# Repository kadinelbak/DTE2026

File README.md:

# DTE 2026

Hardware for the DTE Designathon project.

## EMG + Stretch Sensor Board

KiCad 8 project in [`hardware/emg_board/`](hardware/emg_board/). Open `emg_board.kicad_pro` in KiCad; the symbol and footprint libraries are project-local, so nothing needs to be installed.

```
hardware/emg_board/
├── emg_board.kicad_pro     project
├── emg_board.kicad_sch     schematic
├── emg_board.kicad_pcb     PCB layout
├── EMG_Board.kicad_sym     project symbol library
├── EMG_Board.pretty/       project footprint library (*.kicad_mod)
├── sym-lib-table           points to ${KIPRJMOD}/EMG_Board.kicad_sym
├── fp-lib-table            points to ${KIPRJMOD}/EMG_Board.pretty
└── docs/                   schematic and PCB previews and screenshots
```

The board runs from a 9 V battery through a switch, a reverse-polarity diode and a 7805 regulator into an ESP32 DevKit (38-pin). It carries:

- an EMG front end (instrumentation amp, 8 Hz high-pass, ~800 Hz low-pass, total gain ~1200) on IO34
- a Wheatstone bridge for two stretch sensors on IO35 / IO33
- a potentiometer on IO32
- three indicator LEDs on IO25 / IO26 / IO27

### KiCad screenshots

PCB layout:

Schematic:

## Microcontroller code

Arduino sketches in [`microcontroller_code/`](microcontroller_code/). Each sketch is in a folder with the same name, as the Arduino IDE expects.

- [`WiFi/`](microcontroller_code/WiFi/): ESP32 button that sends a "Danger mode approached, increase stiffness?" alert to the phone and Apple Watch through ntfy.sh. The notification has Increase stiffness and Decrease stiffness buttons that change the stiffness level (0 to 5) on the ESP32, which confirms with a follow-up notification. The LEDs show the stiffness level: green for low (0-1), yellow for medium (2-3) and red for high (4-5). Before building, copy `secrets.example.h` to `secrets.h` and put your WiFi name and password in it. `secrets.h` is git-ignored so the password stays out of the repo.
- [`EMG/`](microcontroller_code/EMG/): samples the EMG signal on A0 at 1200 Hz, cancels 60 Hz mains hum with a one-cycle comb filter, and prints the smoothed muscle-activity envelope over serial at 115200 baud.
- [`RotationalDrive/`](microcontroller_code/RotationalDrive/): reads the outside stretch sensor on A1, zeroes at neutral, and lights a blue warning LED and a blinking red danger LED as the ankle rolls past the limits. Type an angle over serial to calibrate it to degrees (saved to EEPROM), or `z` to re-zero.

## CAD

SolidWorks files for the hydraulic right foot brace are in [`cad/hydraulic_brace/`](cad/hydraulic_brace/): the assembly (`hydraulics brace Assem.SLDASM`), the brace body (`hydraulic right foot brace`), `bottom brace`, `BottomBraceHydraulics`, `InnerBore`, `OuterBore` and `Gasket`. Keep the file names as they are, because the assembly finds its parts by name.

## Images

- [`images/model/`](images/model/): SolidWorks render of the full brace assembly.

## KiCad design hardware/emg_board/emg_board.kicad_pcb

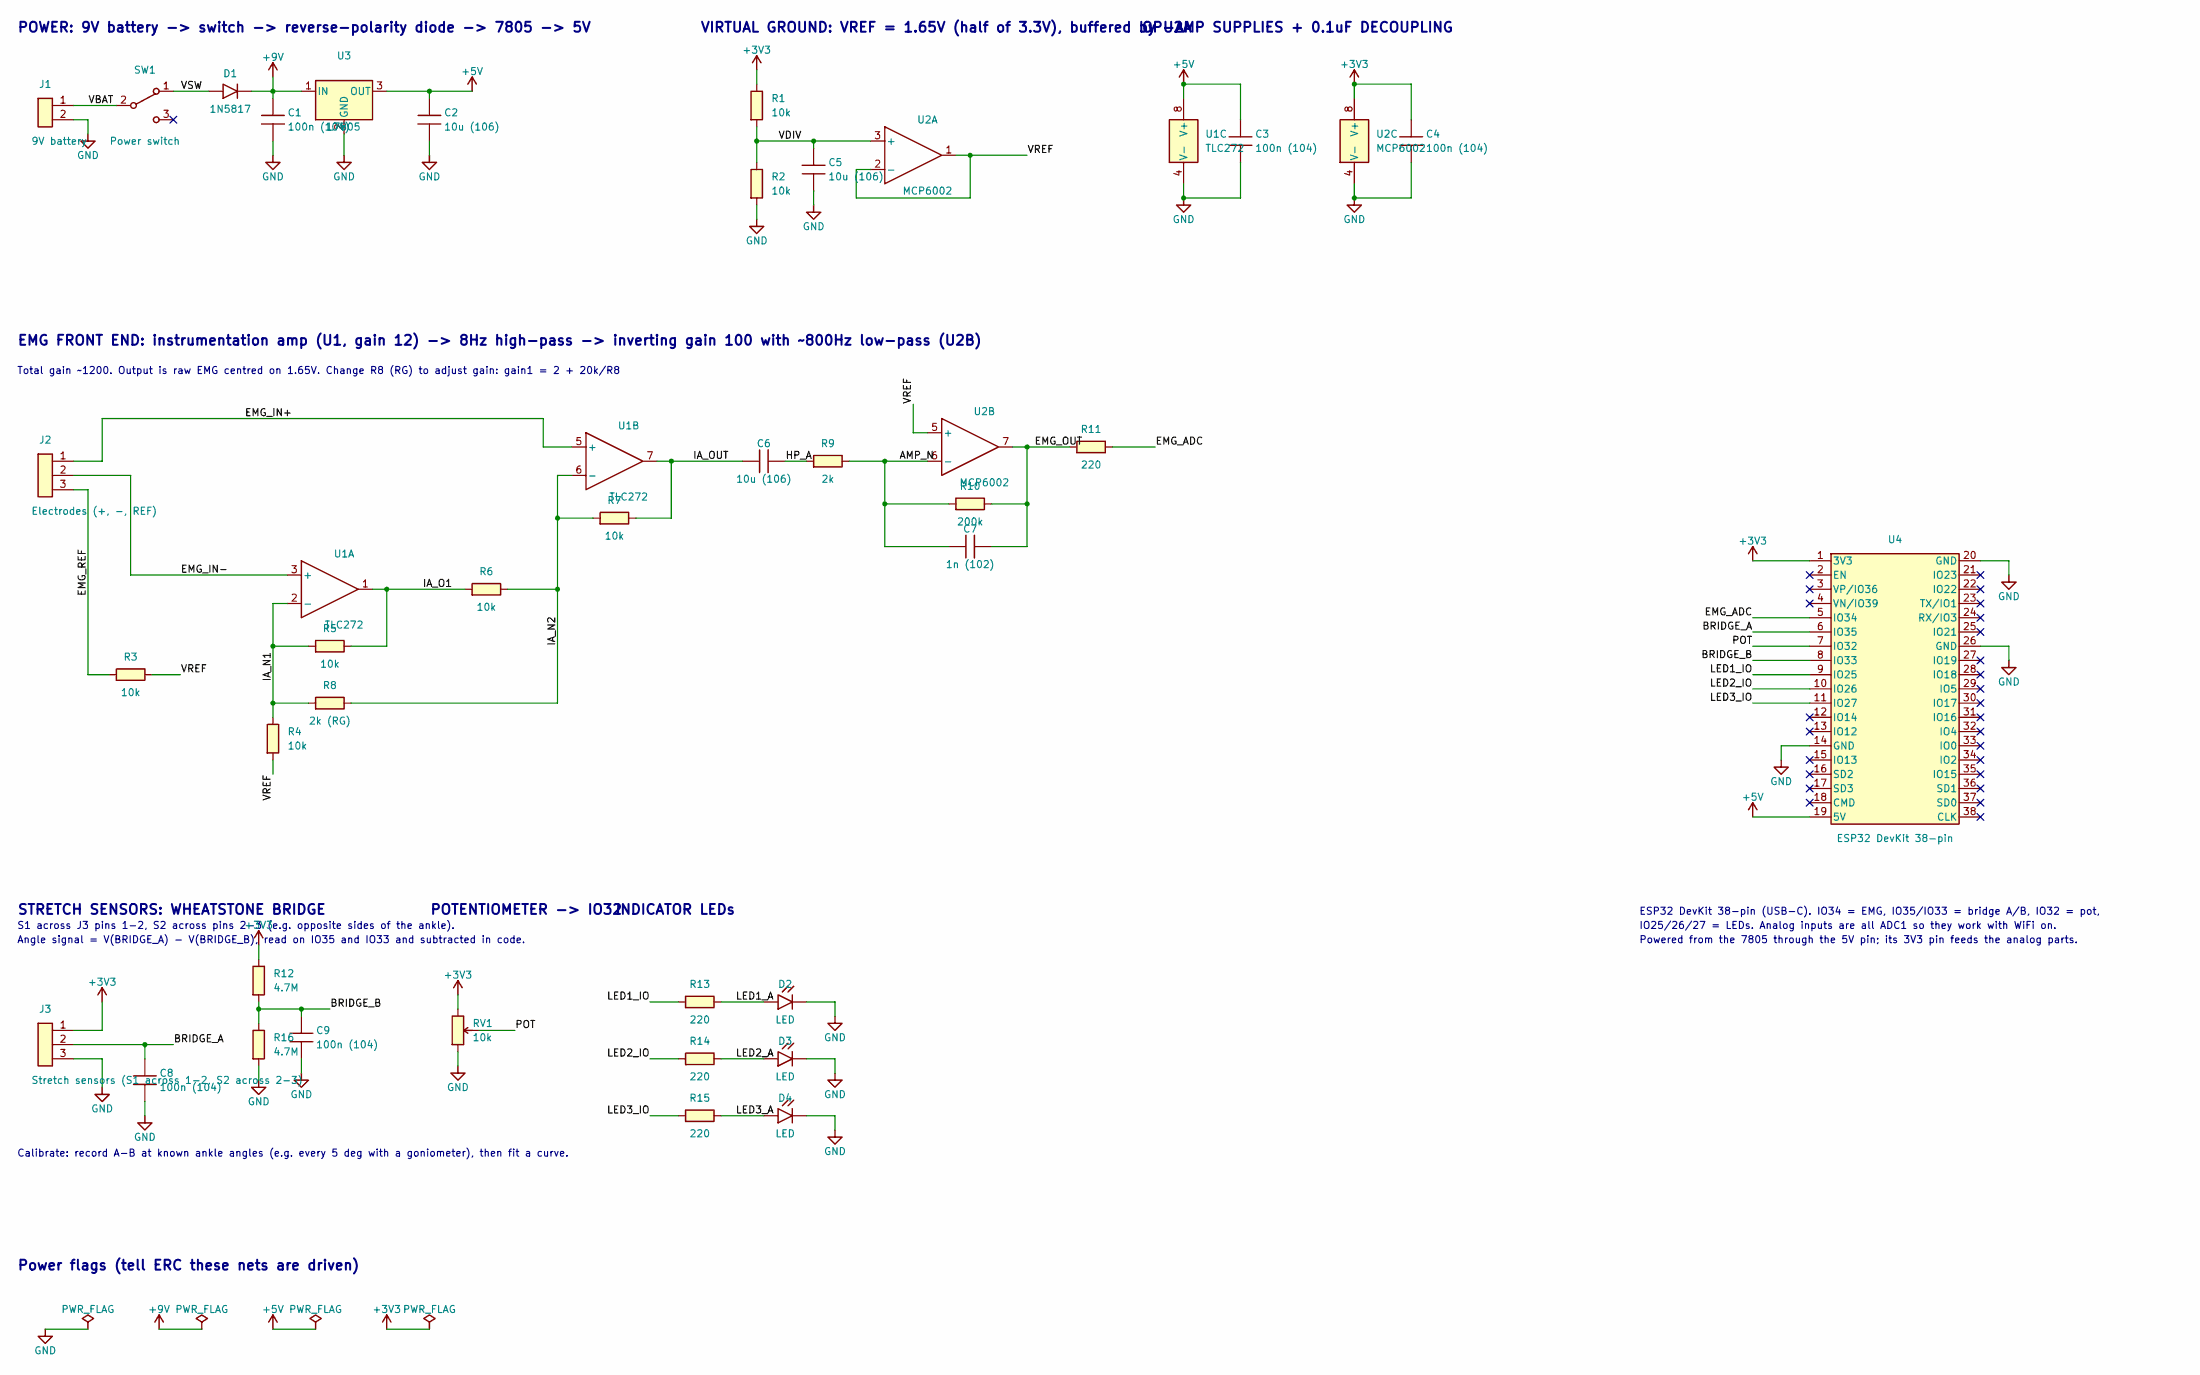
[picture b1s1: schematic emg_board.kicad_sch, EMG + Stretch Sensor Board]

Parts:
C1, C3, C4, C8, C9: 100n (104); C_Disc_P5.08mm
C2, C5, C6: 10u (106); C_Disc_P5.08mm
C7: 1n (102); C_Disc_P5.08mm
D1: 1N5817; D_DO-41_P10.16mm
D2, D3, D4: LED; LED_D5.0mm
J1: 9V battery; TerminalBlock_1x02_P5.08mm
J2: Electrodes (+, -, REF); TerminalBlock_1x03_P5.08mm
J3: Stretch sensors (S1 across 1-2, S2 across 2-3); TerminalBlock_1x03_P5.08mm
R1, R2, R3, R4, R5, R6, R7: 10k; R_Axial_P10.16mm
R8: 2k (RG); R_Axial_P10.16mm
R9: 2k; R_Axial_P10.16mm
R10: 200k; R_Axial_P10.16mm
R11, R13, R14, R15: 220; R_Axial_P10.16mm
R12, R16: 4.7M; R_Axial_P10.16mm
RV1: 10k; Potentiometer_Inline_P2.54mm
SW1: Power switch; SW_Slide_SPDT_P2.54mm
U1: TLC272; DIP-8_W7.62mm
U2: MCP6002; DIP-8_W7.62mm
U3: L7805; TO-220-3_Vertical
U4: ESP32 DevKit 38-pin; ESP32_DevKitC_38pin_W25.4mm

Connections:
+3V3: C4.1, J3.1, R1.1, R12.1, RV1.1, U2.8 (V+), U4.1 (3V3)
+5V: C2.1, C3.1, U1.8 (V+), U3.3 (OUT), U4.19 (5V)
+9V: C1.1, D1.1 (K), U3.1 (IN)
AMP_N: C7.1, R9.2, R10.1, U2.6 (-)
BRIDGE_A: C8.1, J3.2, U4.6 (IO35)
BRIDGE_B: C9.1, R12.2, R16.1, U4.8 (IO33)
EMG_ADC: R11.2, U4.5 (IO34)
EMG_IN+: J2.1, U1.5 (+)
EMG_IN-: J2.2, U1.3 (+)
EMG_OUT: C7.2, R10.2, R11.1, U2.7
EMG_REF: J2.3, R3.1
GND: C1.2, C2.2, C3.2, C4.2, C5.2, C8.2, C9.2, D2.1 (K), D3.1 (K), D4.1 (K), J1.2, J3.3, R2.2, R16.2, RV1.3, U1.4 (V-), U2.4 (V-), U3.2 (GND), U4.14 (GND), U4.20 (GND), U4.26 (GND)
HP_A: C6.2, R9.1
IA_N1: R4.1, R5.1, R8.1, U1.2 (-)
IA_N2: R6.2, R7.1, R8.2, U1.6 (-)
IA_O1: R5.2, R6.1, U1.1
IA_OUT: C6.1, R7.2, U1.7
LED1_A: D2.2 (A), R13.2
LED1_IO: R13.1, U4.9 (IO25)
LED2_A: D3.2 (A), R14.2
LED2_IO: R14.1, U4.10 (IO26)
LED3_A: D4.2 (A), R15.2
LED3_IO: R15.1, U4.11 (IO27)
POT: RV1.2, U4.7 (IO32)
VBAT: J1.1, SW1.2 (B)
VDIV: C5.1, R1.2, R2.1, U2.3 (+)
VREF: R3.2, R4.2, U2.1, U2.2 (-), U2.5 (+)
VSW: D1.2 (A), SW1.1 (A)

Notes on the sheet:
POWER: 9V battery -> switch -> reverse-polarity diode -> 7805 -> 5V
VIRTUAL GROUND: VREF = 1.65V (half of 3.3V), buffered by U2A
OP-AMP SUPPLIES + 0.1uF DECOUPLING
EMG FRONT END: instrumentation amp (U1, gain 12) -> 8Hz high-pass -> inverting gain 100 with ~800Hz low-pass (U2B)
Total gain ~1200. Output is raw EMG centred on 1.65V. Change R8 (RG) to adjust gain: gain1 = 2 + 20k/R8
STRETCH SENSORS: WHEATSTONE BRIDGE
S1 across J3 pins 1-2, S2 across pins 2-3 (e.g. opposite sides of the ankle).
Angle signal = V(BRIDGE_A) - V(BRIDGE_B), read on IO35 and IO33 and subtracted in code.
Calibrate: record A-B at known ankle angles (e.g. every 5 deg with a goniometer), then fit a curve.
POTENTIOMETER -> IO32
INDICATOR LEDs
ESP32 DevKit 38-pin (USB-C). IO34 = EMG, IO35/IO33 = bridge A/B, IO32 = pot,
IO25/26/27 = LEDs. Analog inputs are all ADC1 so they work with WiFi on.
Powered from the 7805 through the 5V pin; its 3V3 pin feeds the analog parts.
Power flags (tell ERC these nets are driven)

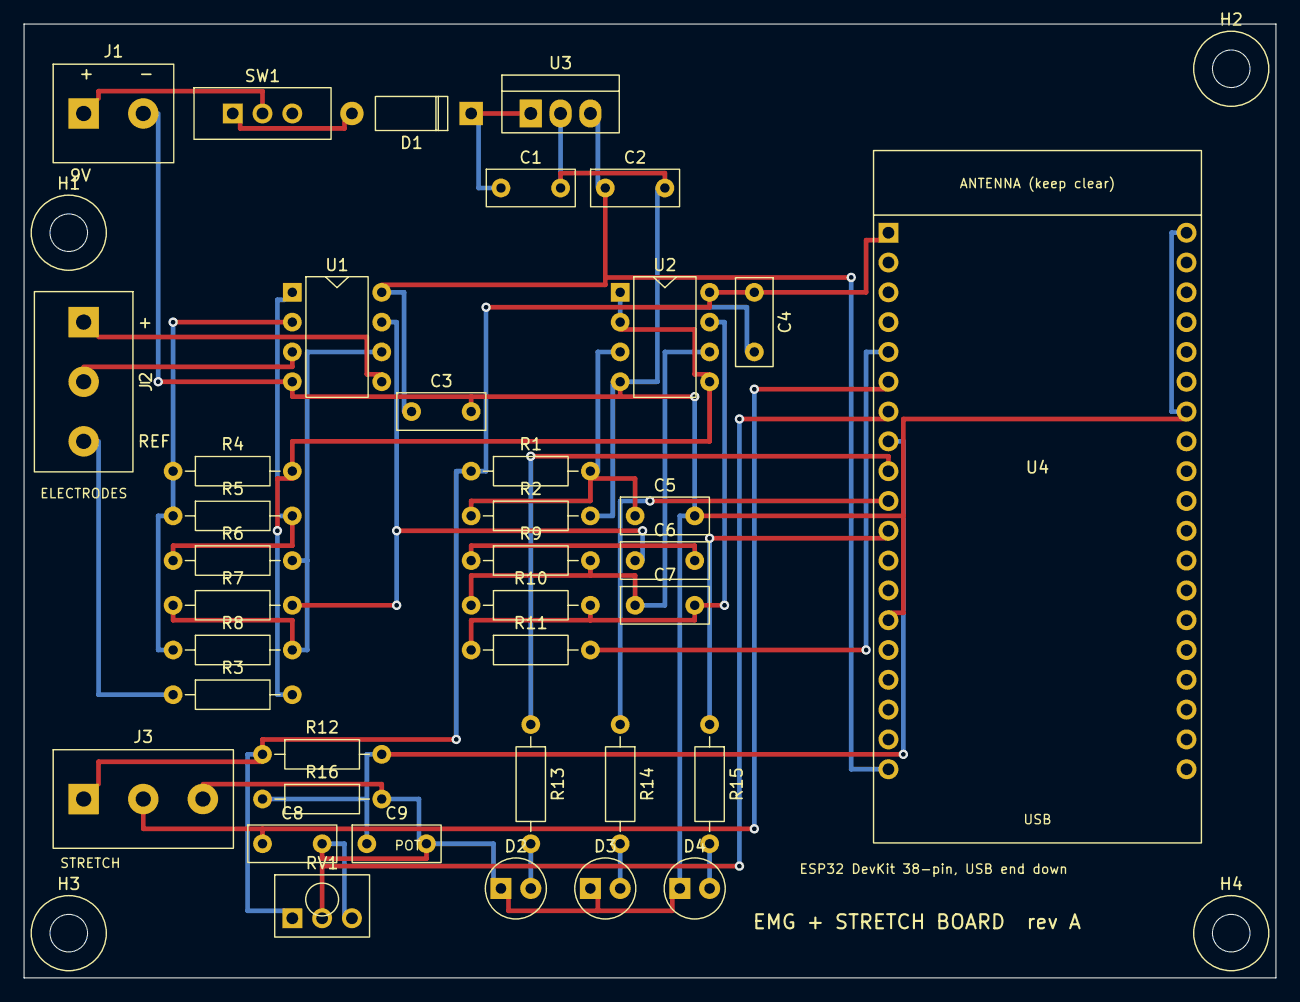
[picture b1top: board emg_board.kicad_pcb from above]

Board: 2 copper layers, 106.7 x 81.3 mm, 42 parts (0 on the bottom side), 28 nets.

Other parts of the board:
H1, H2, H3, H4: MountingHole_3.2mm
